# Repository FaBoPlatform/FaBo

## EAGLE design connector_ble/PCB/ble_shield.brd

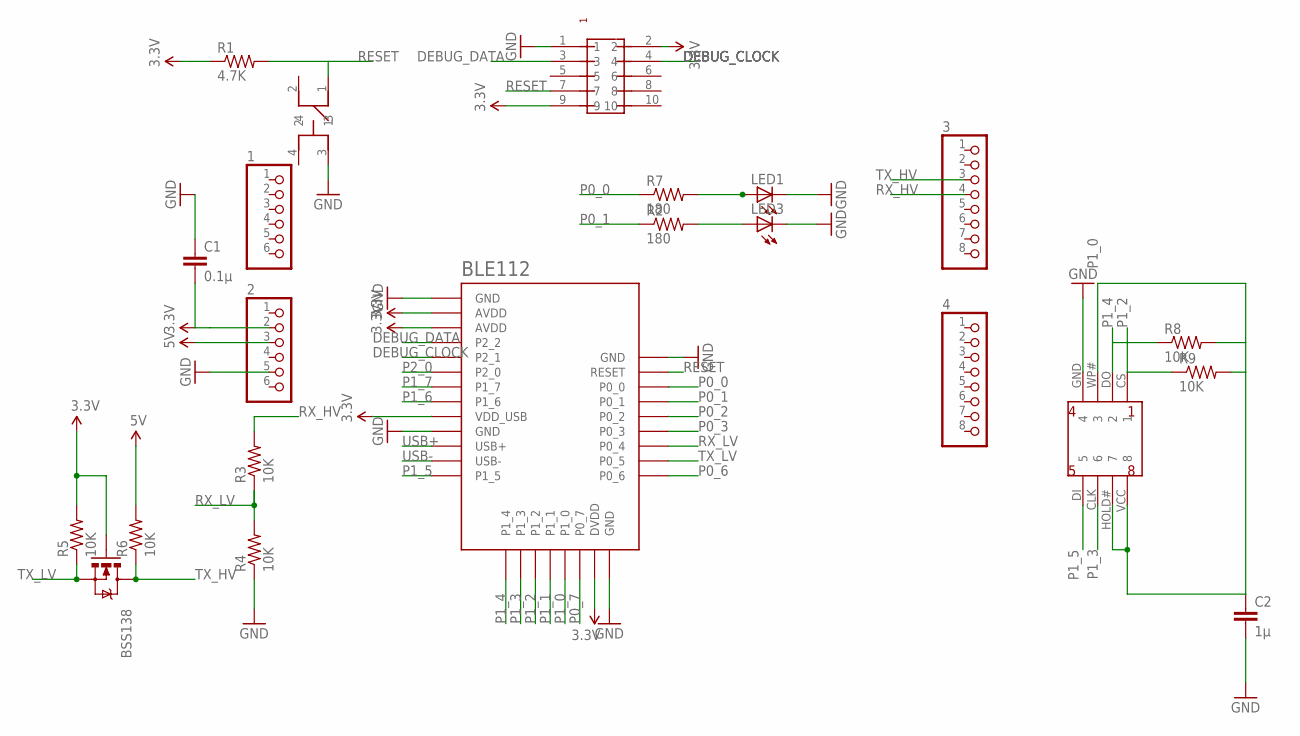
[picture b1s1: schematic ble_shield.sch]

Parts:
1, 2: PINHD-1X6CB; 1X06-CLEANBIG
3, 4: PINHD-1X8CLEANBIG; 1X08-CLEANBIG
BLE112: SF-BLUEGIGA_BLE112-A-VISUAL; SF-BLUEGIGA_BLE112-A
BSS138: MOSFET-NCHANNELSMD; SOT23-3
C1: 0.1μ; 0603-CAP
C2: 1μ; 0603-CAP
LED1, LED3: LED_ESML0603; LED_SML0603
R1: 4.7K; 0603-RES
R2, R7: 180; 0603-RES
R3, R4, R5, R6, R8, R9: 10K; 0603-RES
U$1: PIN-HEADER-SMT(1.27MM)2X5
U$4: SWITCH-LS6J2M-T; SWICTH-LS6J2M-T
U$7: FLASH-MEMORY-2M(WINBOND)

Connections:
3.3V: 2.2, BLE112.AVDD1 (AVDD), BLE112.AVDD2 (AVDD), BLE112.DVDD, BLE112.VDD_USB, BSS138.1 (G), C1.2, R1.1, R5.2, U$1.2, U$1.9
5V: 2.3, R6.2
DEBUG_CLOCK: BLE112.P2_1, U$1.4
DEBUG_DATA: BLE112.P2_2, U$1.3
GND: 2.5, BLE112.GND1 (GND), BLE112.GND2 (GND), BLE112.GND3 (GND), BLE112.GND4 (GND), C1.1, C2.2, LED1.C, LED3.C, R4.1, U$1.1, U$4.3, U$7.GND (4)
unnamed: LED1.A, R7.2
unnamed: LED3.A, R2.2
P0_0: BLE112.P0_0, R7.1
P0_1: BLE112.P0_1, R2.1
P0_2: BLE112.P0_2
P0_3: BLE112.P0_3
P0_6: BLE112.P0_6
P0_7: BLE112.P0_7
P1_0: BLE112.P1_0, C2.1, R8.2, R9.2, U$7.HOLD# (7), U$7.VCC (8), U$7.WP# (3)
P1_1: BLE112.P1_1
P1_2: BLE112.P1_2, R9.1, U$7.CS (1)
P1_3: BLE112.P1_3, U$7.CLK (6)
P1_4: BLE112.P1_4, R8.1, U$7.DO (2)
P1_5: BLE112.P1_5, U$7.DI (5)
P1_6: BLE112.P1_6
P1_7: BLE112.P1_7
P2_0: BLE112.P2_0
RESET: BLE112.RESET, R1.2, U$1.7, U$4.1
RX_HV: 3.4, R3.2
RX_LV: BLE112.P0_4, R3.1, R4.2
TX_HV: 3.3, BSS138.3 (D), R6.1
TX_LV: BLE112.P0_5, BSS138.2 (S), R5.1
USB+: BLE112.USB+
USB-: BLE112.USB-

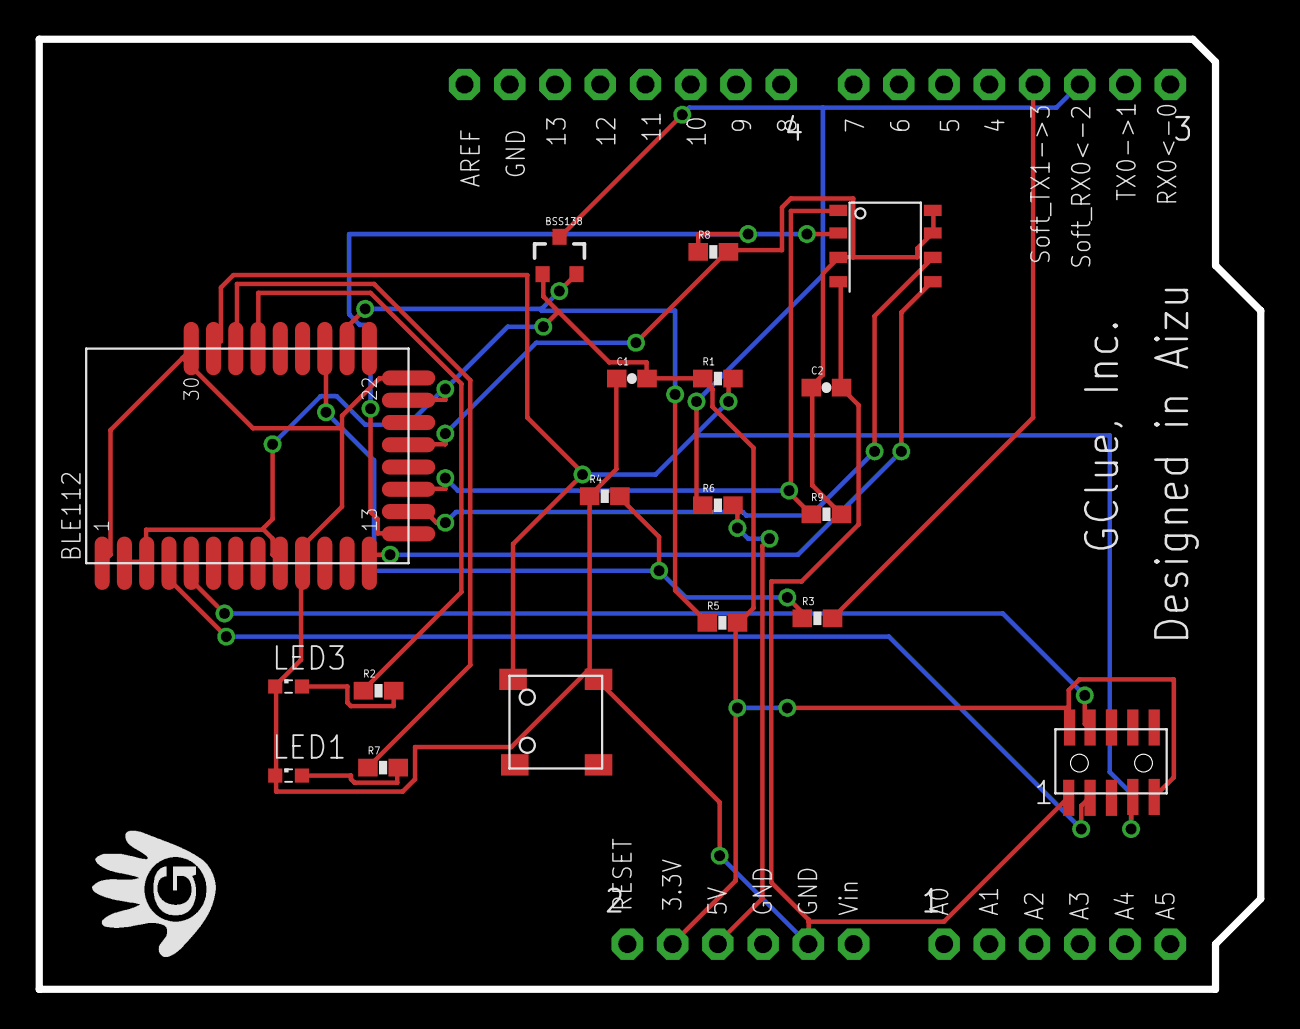
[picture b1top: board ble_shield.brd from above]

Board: 2 copper layers, 68.6 x 53.3 mm, 22 parts (0 on the bottom side), 19 nets.

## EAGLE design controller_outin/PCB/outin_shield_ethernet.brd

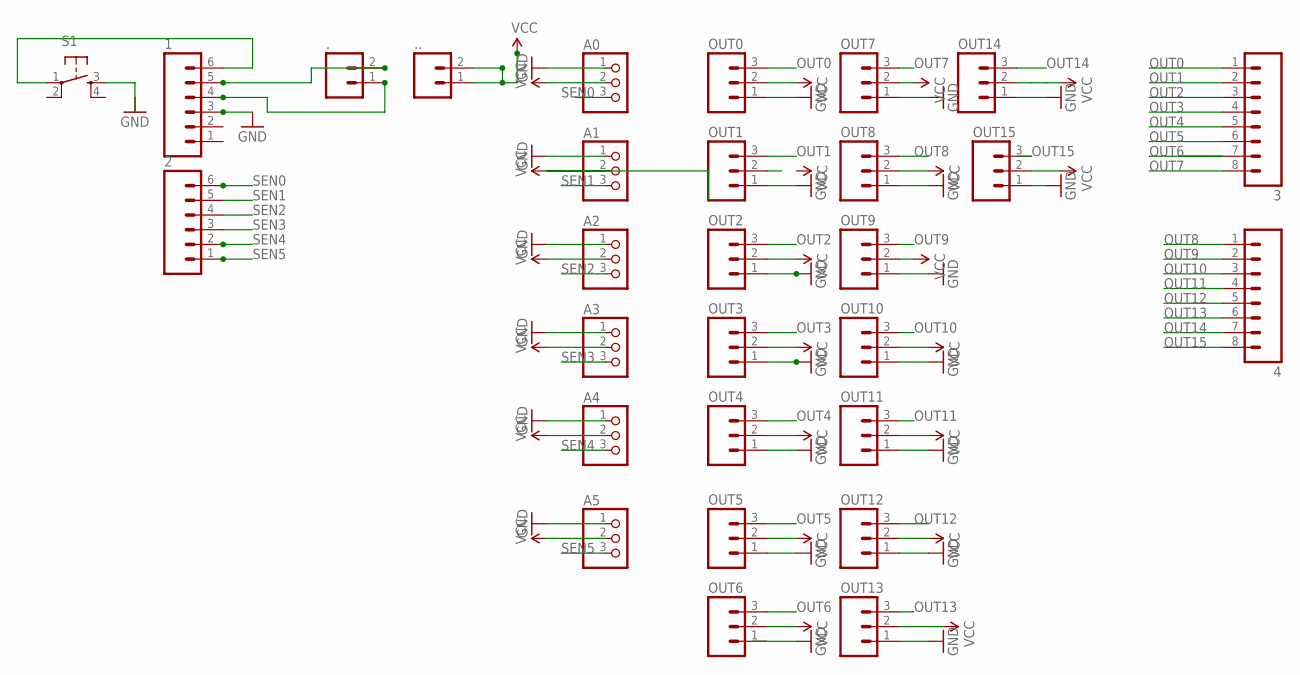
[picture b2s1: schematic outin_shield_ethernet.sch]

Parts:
1, 2: M06SIP; 1X06
3, 4: M081X08; 1X08
., ..: M02LOCK; 1X02_LOCK
A0, A1, A2, A3, A4, A5: PINHD-1X3; 1X03
OUT0, OUT1, OUT2, OUT3, OUT4, OUT5, OUT6, OUT7, OUT8, OUT9, OUT10, OUT11, OUT12, OUT13, OUT14, OUT15: M03PTH; 1X03
S1: TAC_SWITCHPTH; TACTILE-PTH

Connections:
GND: 1.3, A0.1, A1.1, A2.1, A3.1, A4.1, A5.1, OUT0.1, OUT1.1, OUT2.1, OUT3.1, OUT4.1, OUT5.1, OUT7.1, OUT8.1, OUT9.1, OUT10.1, OUT11.1, OUT12.1, OUT13.1, OUT14.1, OUT15.1
unnamed: 1.6, S1.1
unnamed: 1.4, ..1
unnamed: 1.5, ..2
OUT0: 3.1, OUT0.3
OUT1: 3.2, OUT1.3
OUT2: 3.3, OUT2.3
OUT3: 3.4, OUT3.3
OUT4: 3.5, OUT4.3
OUT5: 3.6, OUT5.3
OUT6: 3.7, OUT6.3
OUT7: 3.8, OUT7.3
OUT8: 4.1, OUT8.3
OUT9: 4.2, OUT9.3
OUT10: 4.3, OUT10.3
OUT11: 4.4, OUT11.3
OUT12: 4.5, OUT12.3
OUT13: 4.6, OUT13.3
OUT14: 4.7, OUT14.3
OUT15: 4.8, OUT15.3
SEN0: 2.6, A0.3
SEN1: 2.5, A1.3
SEN2: 2.4, A2.3
SEN3: 2.3, A3.3
SEN4: 2.2, A4.3
SEN5: 2.1, A5.3
VCC: ...1, ...2, A0.2, A1.2, A2.2, A3.2, A4.2, A5.2, OUT0.2, OUT2.2, OUT3.2, OUT4.2, OUT5.2, OUT6.2, OUT7.2, OUT8.2, OUT9.2, OUT10.2, OUT11.2, OUT12.2, OUT13.2, OUT14.2, OUT15.2

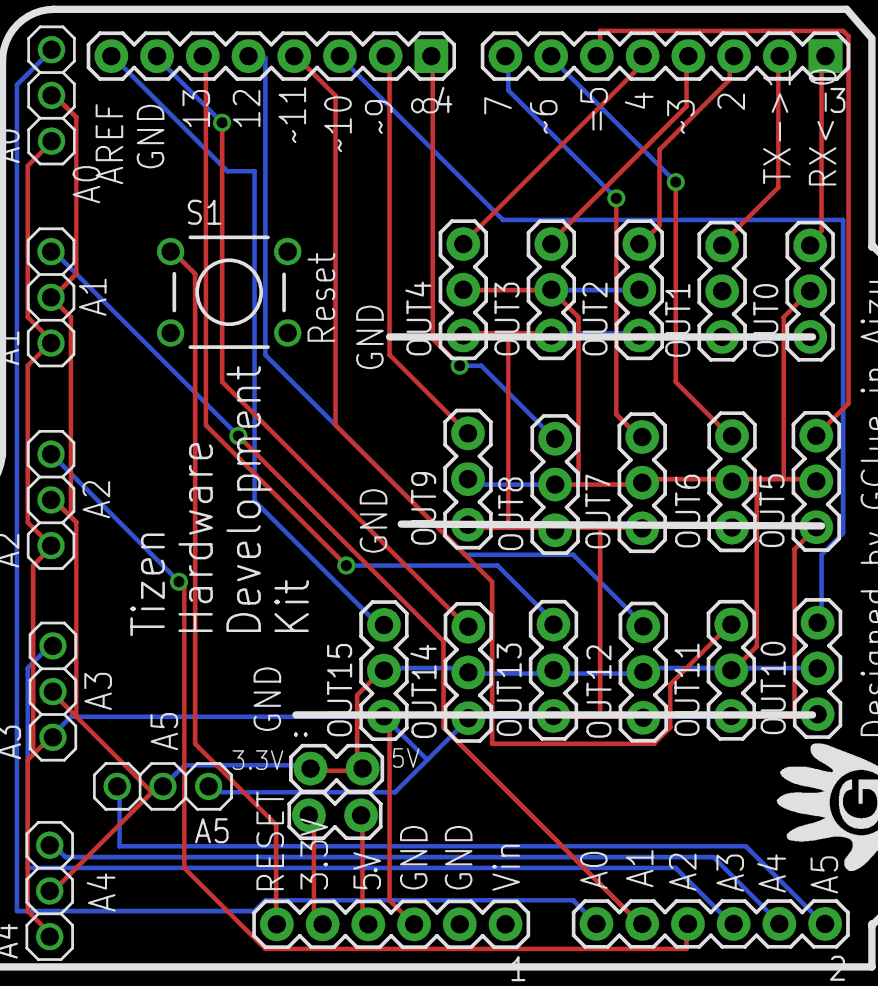
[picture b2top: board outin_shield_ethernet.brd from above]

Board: 2 copper layers, 29 parts (0 on the bottom side), 27 nets.

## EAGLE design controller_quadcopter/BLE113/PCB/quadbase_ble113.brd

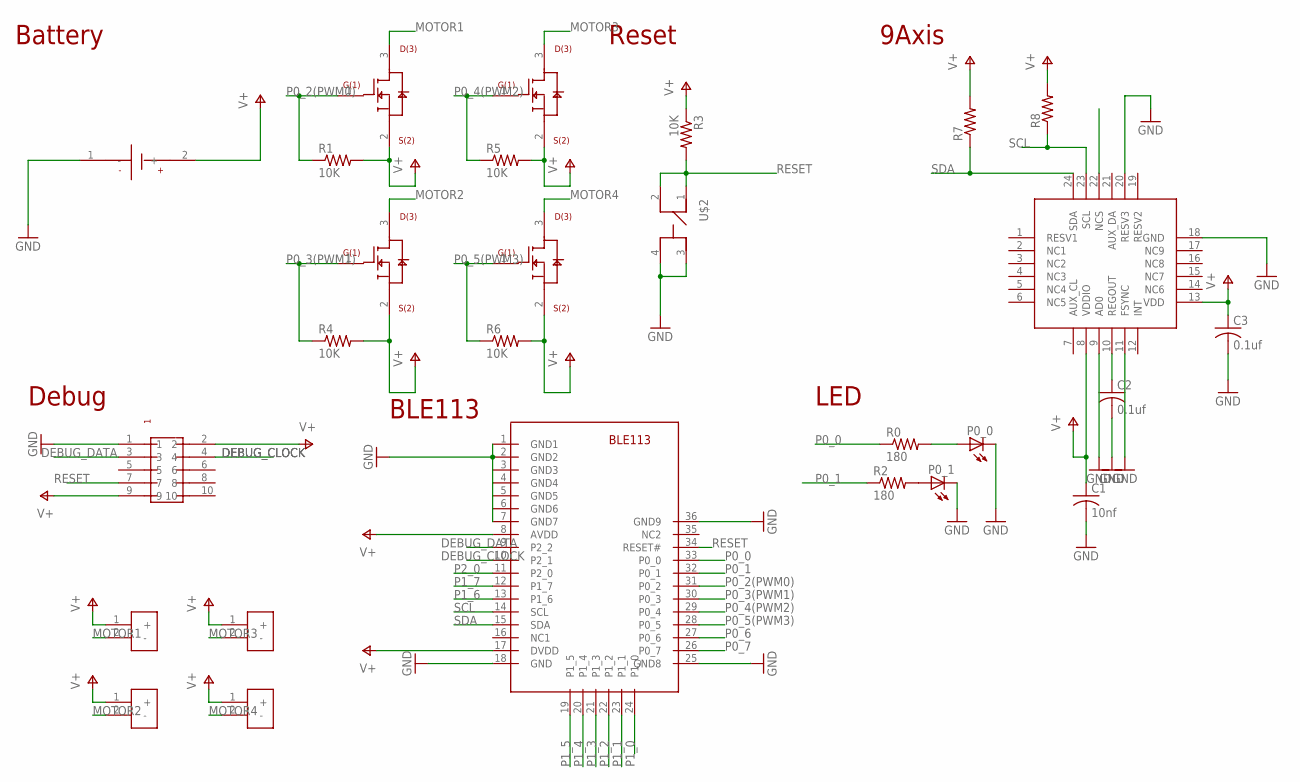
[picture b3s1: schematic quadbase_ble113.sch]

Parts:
C1: 10nf; C0603
C2, C3: 0.1uf; C0603
MOTOR1, MOTOR2, MOTOR3, MOTOR4: SMD-MOTOR
P0_0, P0_1: LEDCHIP-LED0603; CHIP-LED0603
R0, R2: 180; 0603-RES
R1, R4, R5, R6: 10K; R0603
R3: 10K; 0603-RES
R7, R8: R-US_R0603; R0603
U$1: SMD-SUPPLY; SMD_SUPPLY
U$2: SWITCH-LS6J2M-T
U$3: PIN-HEADER-SMT(1.27MM)2X5
U$4: BLE113
U$5, U$7, U$8, U$9: VISHAY-SI2318CDS
U$10: INVENSENSE-MPU9250

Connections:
DEBUG_CLOCK: U$3.4, U$4.10 (P2_1)
DEBUG_DATA: U$3.3, U$4.9 (P2_2)
GND: C1.2, C2.2, C3.2, P0_0.C, P0_1.C, U$1.1 (-), U$2.3, U$2.4, U$3.1, U$4.1 (GND1), U$4.2 (GND2), U$4.3 (GND3), U$4.4 (GND4), U$4.5 (GND5), U$4.6 (GND6), U$4.7 (GND7), U$4.18 (GND), U$4.25 (GND8), U$4.36 (GND9), U$10.9 (AD0), U$10.11 (FSYNC), U$10.18 (GND), U$10.20 (RESV3)
MOTOR1: MOTOR1.2 (-), U$5.3
MOTOR2: MOTOR2.2 (-), U$7.3
MOTOR3: MOTOR3.2 (-), U$8.3
MOTOR4: MOTOR4.2 (-), U$9.3
unnamed: C2.1, U$10.10 (REGOUT)
unnamed: P0_0.A, R0.2
unnamed: P0_1.A, R2.2
P0_0: R0.1, U$4.33 (P0_0)
P0_1: R2.1, U$4.32 (P0_1)
P0_2(PWM0): R1.1, U$4.31 (P0_2), U$5.1
P0_3(PWM1): R4.1, U$4.30 (P0_3), U$7.1
P0_4(PWM2): R5.1, U$4.29 (P0_4), U$8.1
P0_5(PWM3): R6.1, U$4.28 (P0_5), U$9.1
P0_6: U$4.27 (P0_6)
P0_7: U$4.26 (P0_7)
P1_0: U$4.24 (P1_0)
P1_1: U$4.23 (P1_1)
P1_2: U$4.22 (P1_2)
P1_3: U$4.21 (P1_3)
P1_4: U$4.20 (P1_4)
P1_5: U$4.19 (P1_5)
P1_6: U$4.13 (P1_6)
P1_7: U$4.12 (P1_7)
P2_0: U$4.11 (P2_0)
RESET: R3.2, U$2.1, U$2.2, U$3.7, U$4.34 (RESET#)
SCL: R8.1, U$4.14 (SCL), U$10.23 (SCL)
SDA: R7.1, U$4.15 (SDA), U$10.24 (SDA)
V+: C1.1, C3.1, MOTOR1.1 (+), MOTOR2.1 (+), MOTOR3.1 (+), MOTOR4.1 (+), R1.2, R3.1, R4.2, R5.2, R6.2, R7.2, R8.2, U$1.2 (+), U$3.2, U$3.9, U$4.8 (AVDD), U$4.17 (DVDD), U$5.2, U$7.2, U$8.2, U$9.2, U$10.8 (VDDIO), U$10.13 (VDD)

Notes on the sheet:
Reset
Battery
Debug
BLE113
LED
9Axis

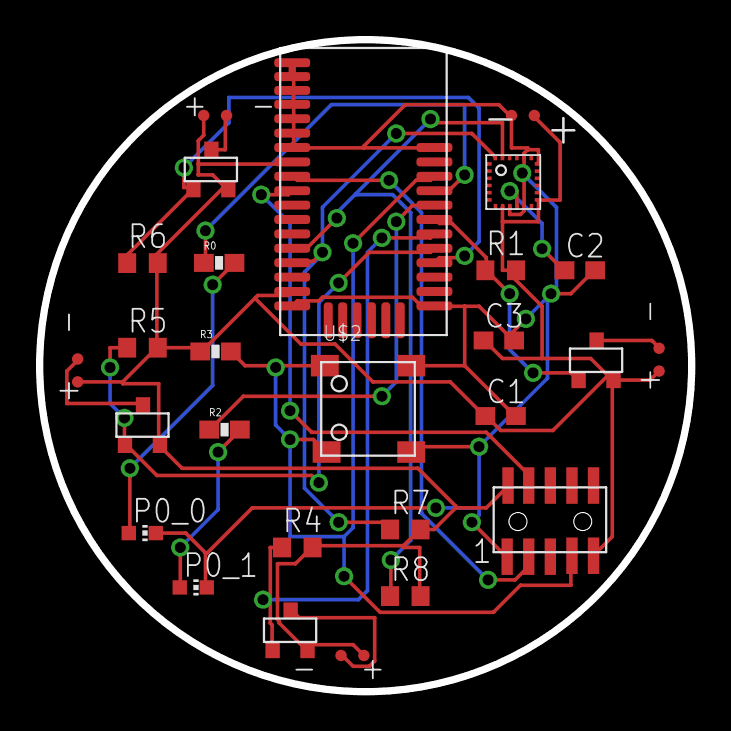
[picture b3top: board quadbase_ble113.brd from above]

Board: 2 copper layers, 36.2 x 36.2 mm, 27 parts (0 on the bottom side), 20 nets.

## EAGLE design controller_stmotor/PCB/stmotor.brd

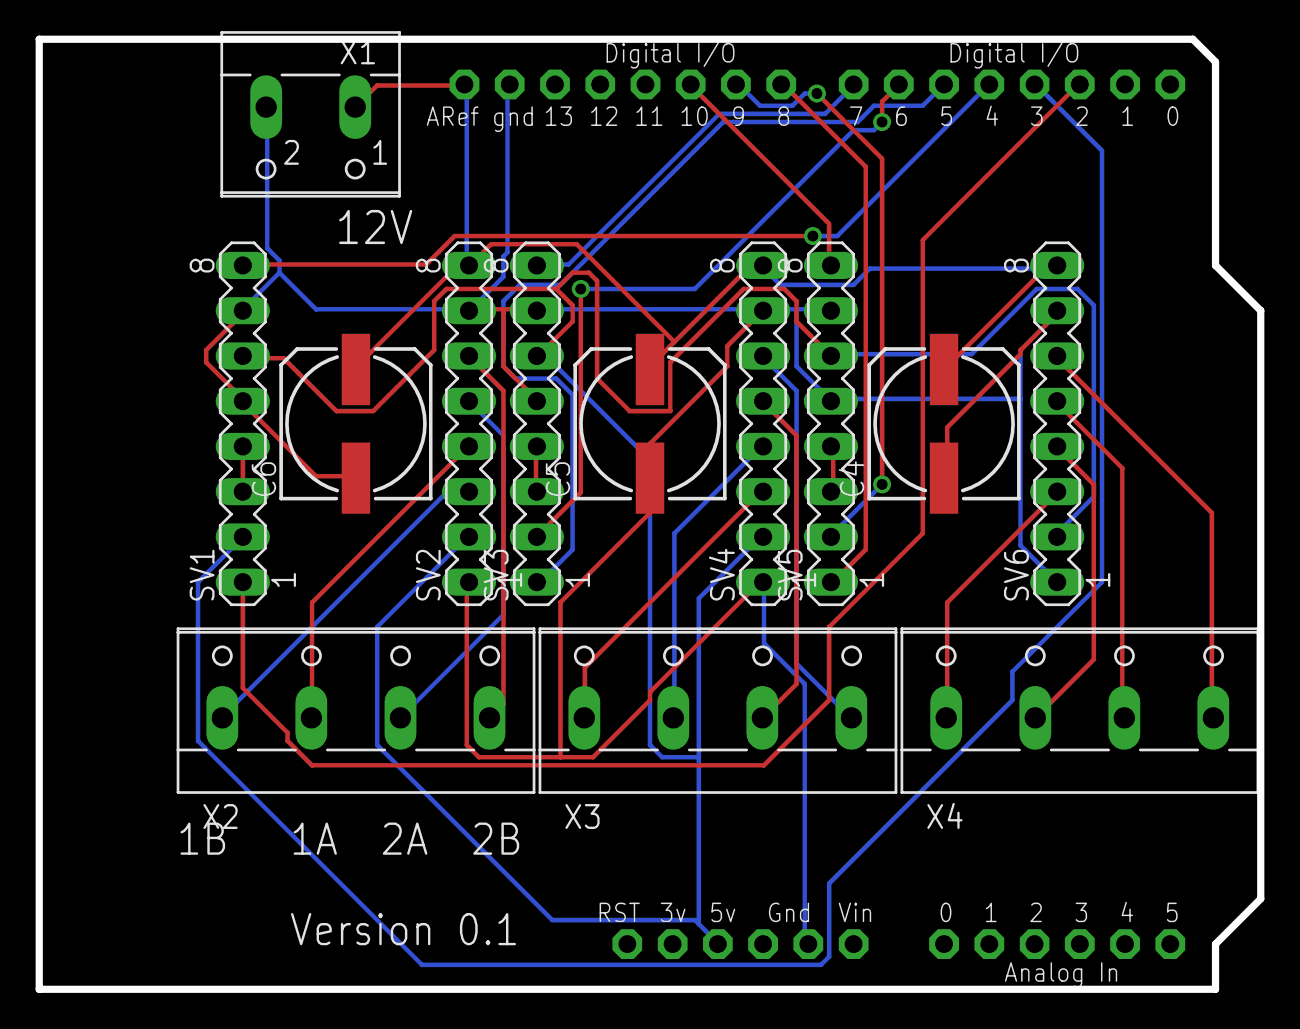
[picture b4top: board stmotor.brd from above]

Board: 2 copper layers, 68.6 x 53.3 mm, 14 parts (0 on the bottom side), 27 nets.

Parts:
C4, C5, C6: 153CLV-0807
SV1, SV2, SV3, SV4, SV5, SV6: MA08-1
U$1: ARDUINO-NOHOLE
X1: W237-102
X2, X3, X4: W237-4

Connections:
+5V: SV1.6, SV2.2, SV3.6, SV4.2, SV5.6, SV6.2, U$1.5V
+12V: C4.+, C5.+, C6.+, SV2.8, SV4.8, SV6.8, U$1.AREF, X1.1
GND: C4.-, C5.-, C6.-, SV1.5, SV1.7, SV2.1, SV2.7, SV3.5, SV3.7, SV4.1, SV4.7, SV5.5, SV5.7, SV6.1, SV6.7, U$1.GND, U$1.GND1, X1.2
unnamed: SV3.3, SV3.4
unnamed: SV5.3, SV5.4
S1_1A: SV2.4, X2.2
S1_1B: SV2.3, X2.1
S1_2A: SV2.5, X2.3
S1_2B: SV2.6, X2.4
S1_DIR: SV1.1, U$1.D2
S1_EN: SV1.8, U$1.D4
S1_RST: SV1.3, SV1.4
S1_STEP: SV1.2, U$1.D3
S2_1A: SV4.4, X3.2
S2_1B: SV4.3, X3.1
S2_2A: SV4.5, X3.3
S2_2B: SV4.6, X3.4
S2_DIR: SV3.1, U$1.D5
S2_EN: SV3.8, U$1.D7
S2_STEP: SV3.2, U$1.D6
S3_1A: SV6.4, X4.2
S3_1B: SV6.3, X4.1
S3_2A: SV6.5, X4.3
S3_2B: SV6.6, X4.4
S3_DIR: SV5.1, U$1.D8
S3_EN: SV5.8, U$1.D10
S3_STEP: SV5.2, U$1.D9

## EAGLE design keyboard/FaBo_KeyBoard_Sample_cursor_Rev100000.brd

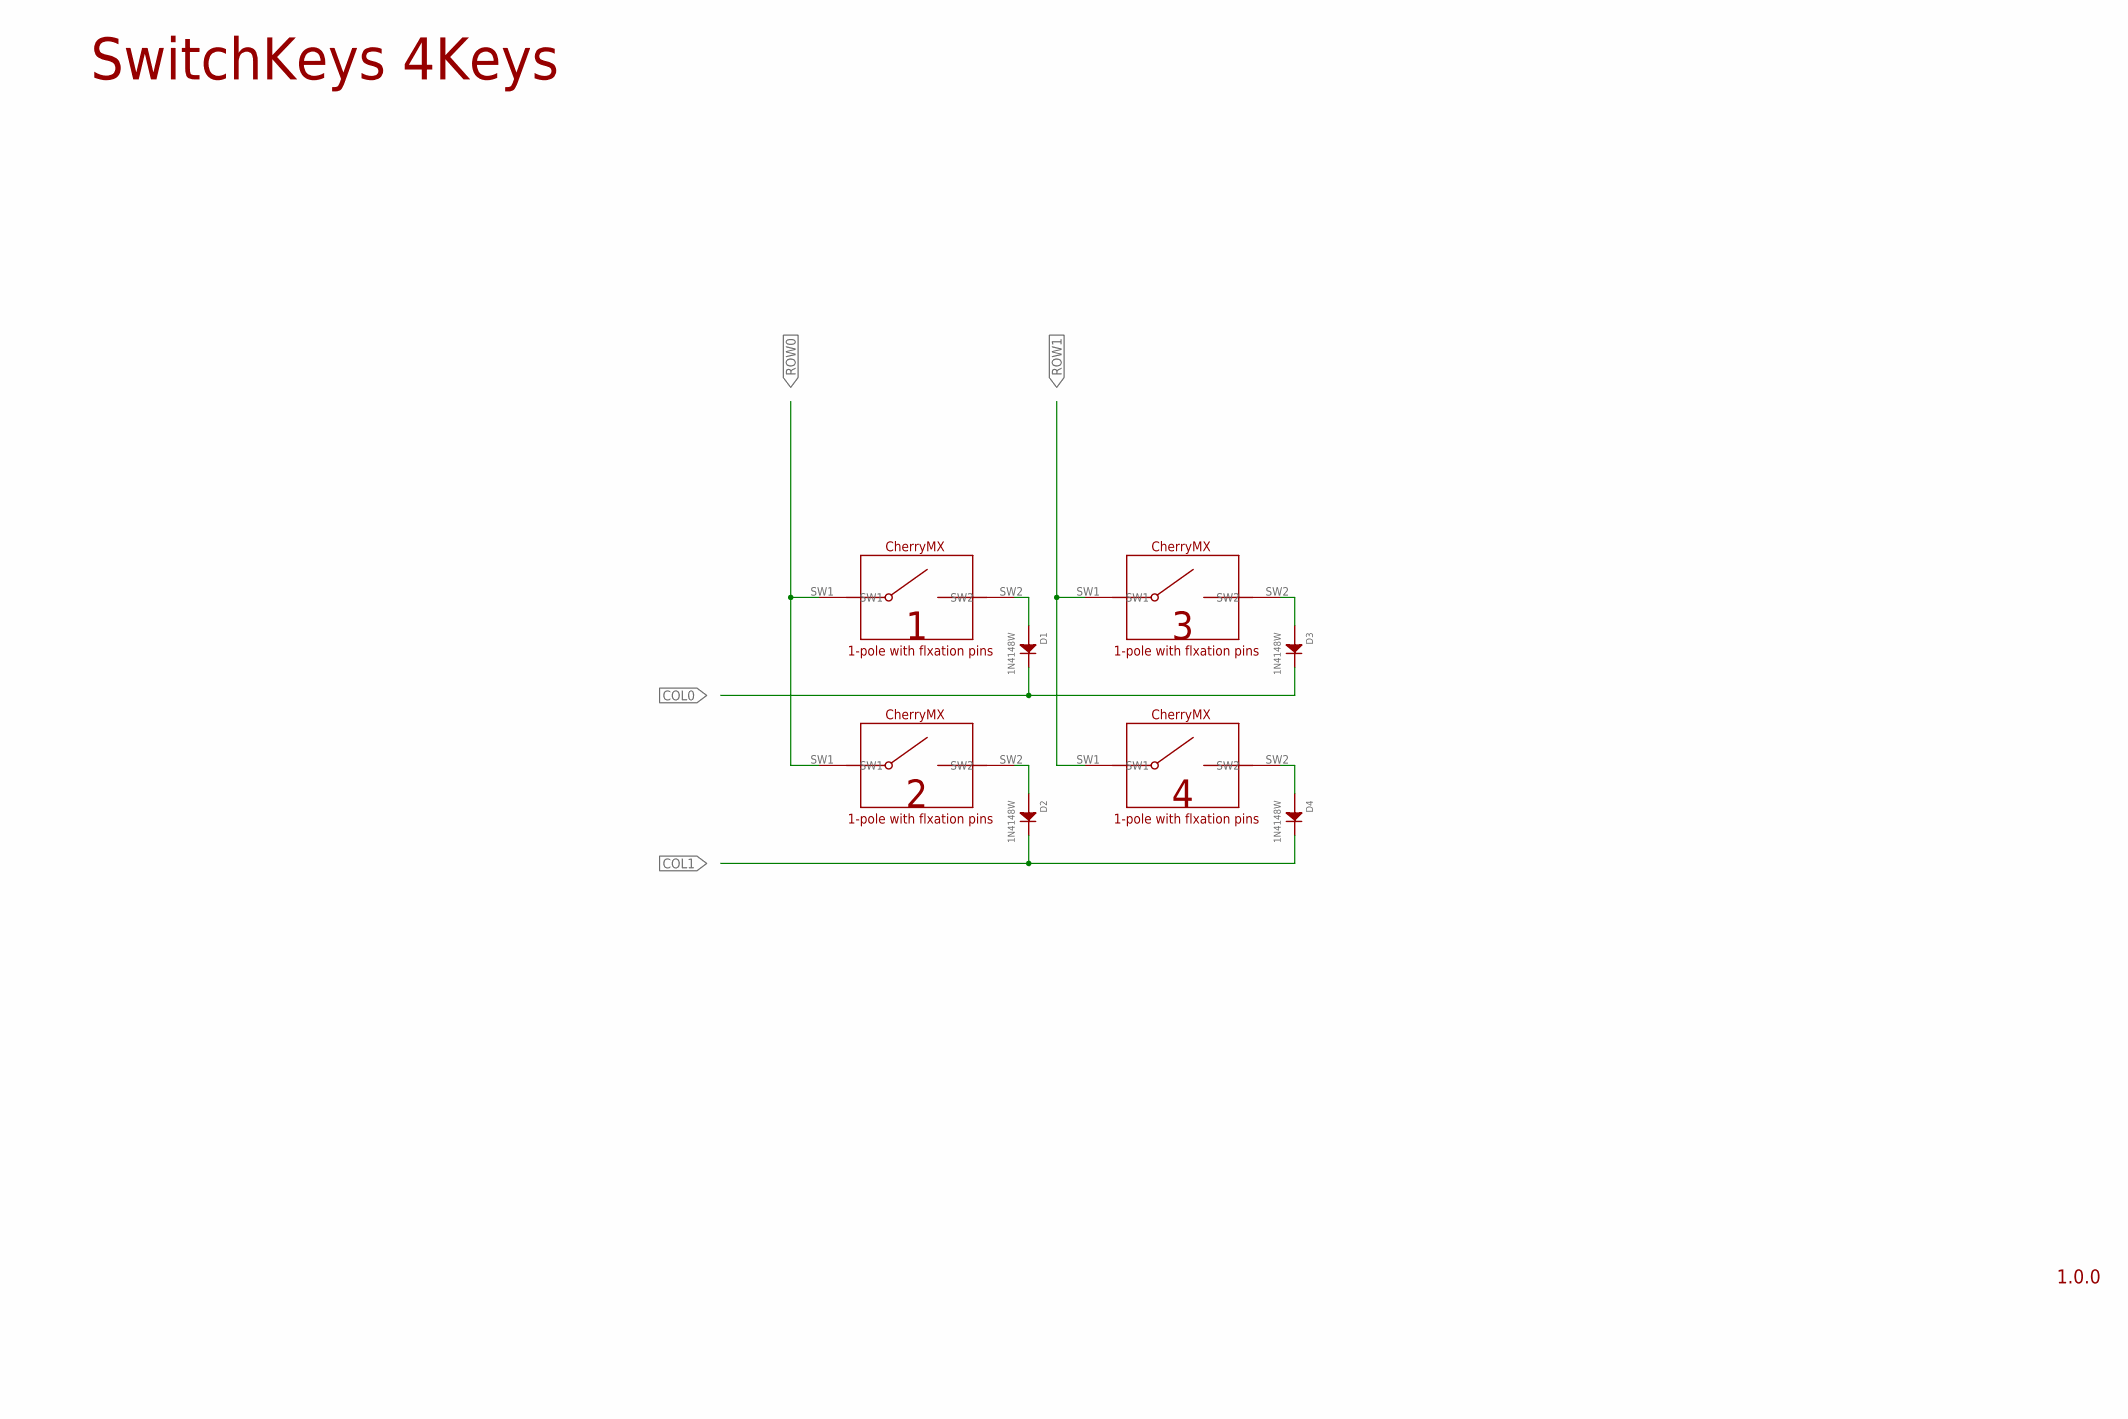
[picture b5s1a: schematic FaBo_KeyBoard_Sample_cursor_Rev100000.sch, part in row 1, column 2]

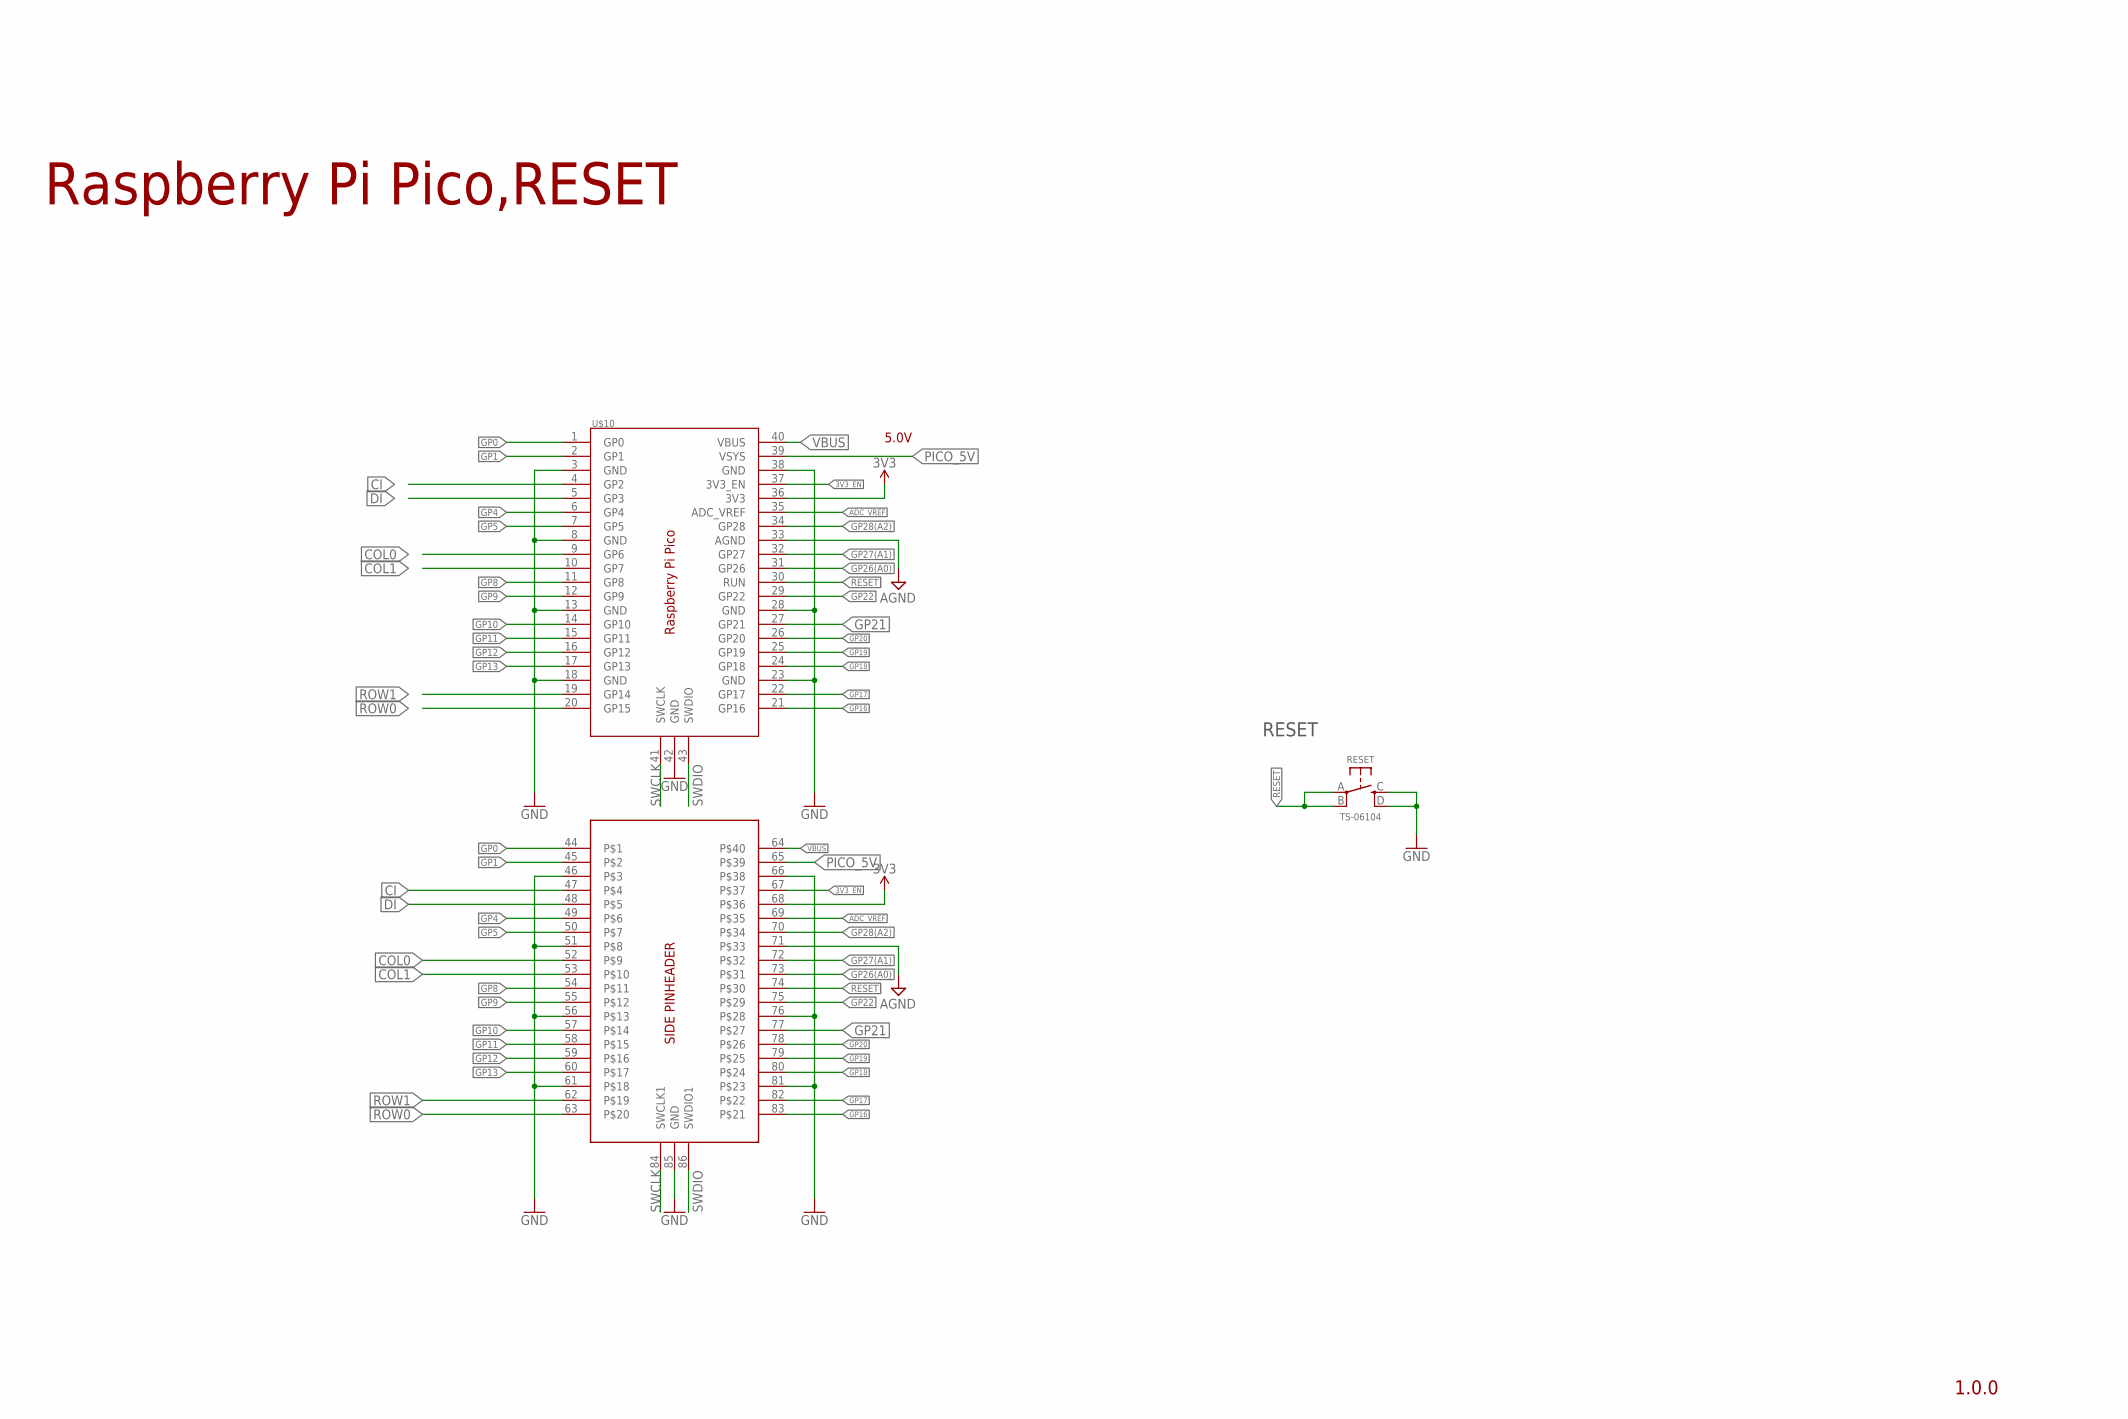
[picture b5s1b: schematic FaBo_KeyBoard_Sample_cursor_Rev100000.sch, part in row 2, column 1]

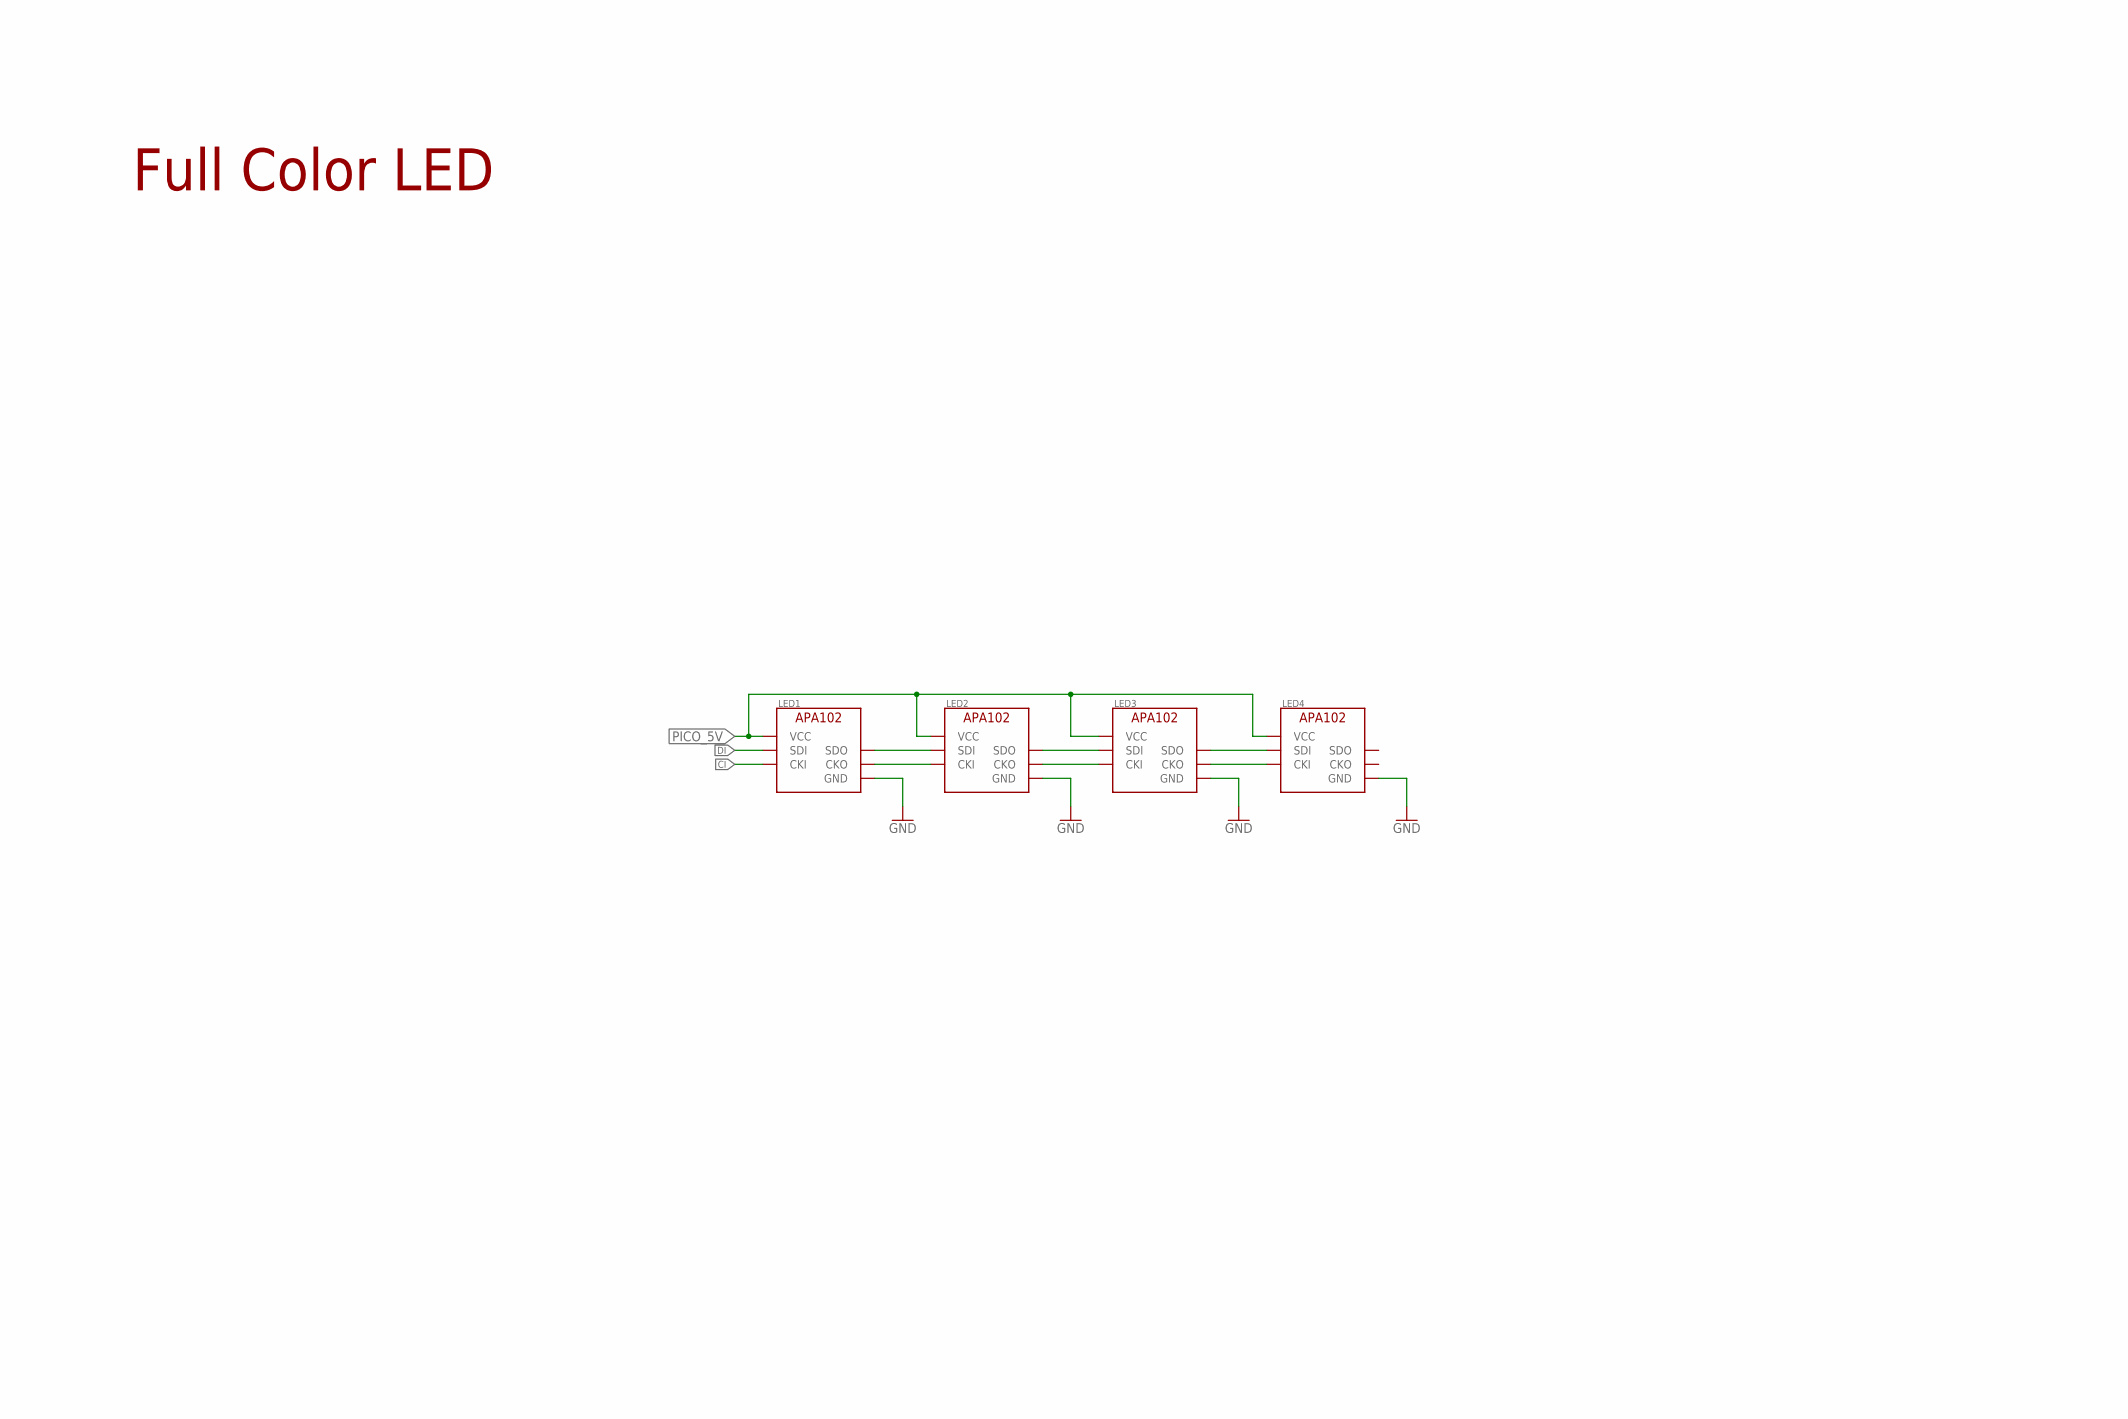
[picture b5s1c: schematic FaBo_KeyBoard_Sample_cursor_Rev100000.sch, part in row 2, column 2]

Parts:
D1, D2, D3, D4: 1N4148W; SOD-123
LED1, LED2, LED3, LED4: APA102_IPIXEL; APA102_2020
RESET: TS-06104
SW1, SW2, SW3, SW4: CHERRYMX_1-POLE_FLXATION_PINS
U$10: RASPBERRY_PI_PICO_BOTH_TH_PINHEADER; RASPBERRY_PI_PICO_HEADER_BOTH

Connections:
3V3: U$10.36 (3V3), U$10.68
3V3_EN: U$10.37 (3V3_EN), U$10.67
ADC_VREF: U$10.35 (ADC_VREF), U$10.69
AGND: U$10.33 (AGND), U$10.71
CI: LED1.CKI, U$10.4 (GP2), U$10.47
CI1: LED1.CKO, LED2.CKI
CI2: LED2.CKO, LED3.CKI
CI3: LED3.CKO, LED4.CKI
COL0: D1.1 (CATHODE), D3.1 (CATHODE), U$10.9 (GP6), U$10.52
COL1: D2.1 (CATHODE), D4.1 (CATHODE), U$10.10 (GP7), U$10.53
DI: LED1.SDI, U$10.5 (GP3), U$10.48
DI1: LED1.SDO, LED2.SDI
DI2: LED2.SDO, LED3.SDI
DI3: LED3.SDO, LED4.SDI
GND: LED1.GND, LED2.GND, LED3.GND, LED4.GND, RESET.C, RESET.D, U$10.3 (GND), U$10.8 (GND), U$10.13 (GND), U$10.18 (GND), U$10.23 (GND), U$10.28 (GND), U$10.38 (GND), U$10.42 (GND), U$10.46, U$10.51, U$10.56, U$10.61, U$10.66, U$10.76, U$10.81, U$10.85 (GND)
GP0: U$10.1 (GP0), U$10.44
GP1: U$10.2 (GP1), U$10.45
GP4: U$10.6 (GP4), U$10.49
GP5: U$10.7 (GP5), U$10.50
GP8: U$10.11 (GP8), U$10.54
GP9: U$10.12 (GP9), U$10.55
GP10: U$10.14 (GP10), U$10.57
GP11: U$10.15 (GP11), U$10.58
GP12: U$10.16 (GP12), U$10.59
GP13: U$10.17 (GP13), U$10.60
GP16: U$10.21 (GP16), U$10.83
GP17: U$10.22 (GP17), U$10.82
GP18: U$10.24 (GP18), U$10.80
GP19: U$10.25 (GP19), U$10.79
GP20: U$10.26 (GP20), U$10.78
GP21: U$10.27 (GP21), U$10.77
GP22: U$10.29 (GP22), U$10.75
GP26(A0): U$10.31 (GP26), U$10.73
GP27(A1): U$10.32 (GP27), U$10.72
GP28(A2): U$10.34 (GP28), U$10.70
unnamed: D1.2 (ANODE), SW1.SW2
unnamed: D2.2 (ANODE), SW2.SW2
unnamed: D3.2 (ANODE), SW3.SW2
unnamed: D4.2 (ANODE), SW4.SW2
PICO_5V: LED1.VCC, LED2.VCC, LED3.VCC, LED4.VCC, U$10.39 (VSYS), U$10.65
RESET: RESET.A, RESET.B, U$10.30 (RUN), U$10.74
ROW0: SW1.SW1, SW2.SW1, U$10.20 (GP15), U$10.63
ROW1: SW3.SW1, SW4.SW1, U$10.19 (GP14), U$10.62
SWCLK: U$10.41 (SWCLK), U$10.84 (SWCLK1)
SWDIO: U$10.43 (SWDIO), U$10.86 (SWDIO1)
VBUS: U$10.40 (VBUS), U$10.64

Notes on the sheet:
1.0.0
Revision
Raspberry Pi Pico,RESET
SwitchKeys 4Keys
1.0.0
FaBo KeyBoard Sample
RESET
5.0V
Full Color LED

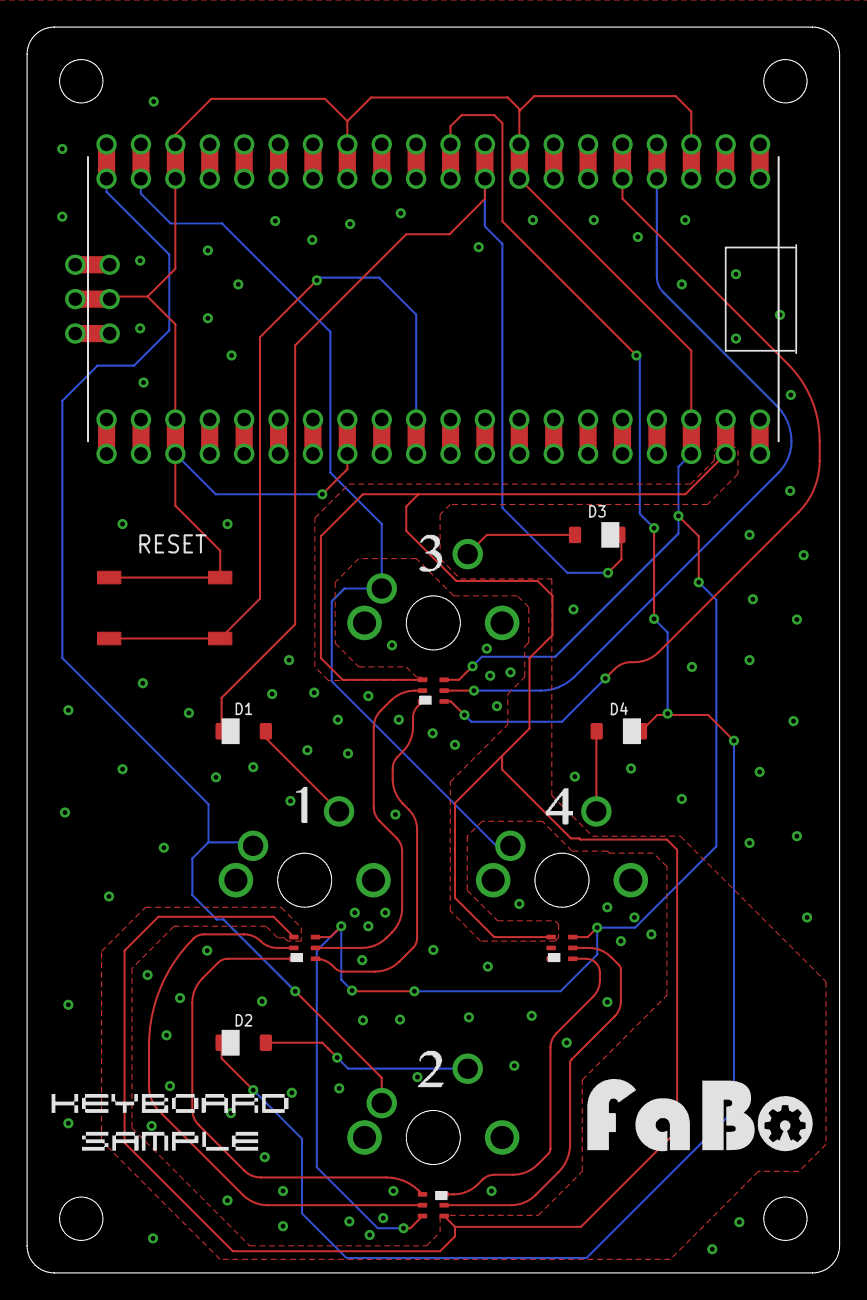
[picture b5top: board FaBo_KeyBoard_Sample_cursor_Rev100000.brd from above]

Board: 2 copper layers, 60.0 x 92.0 mm, 15 parts (0 on the bottom side), 46 nets.

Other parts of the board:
U$1: LOGO_FABO_L

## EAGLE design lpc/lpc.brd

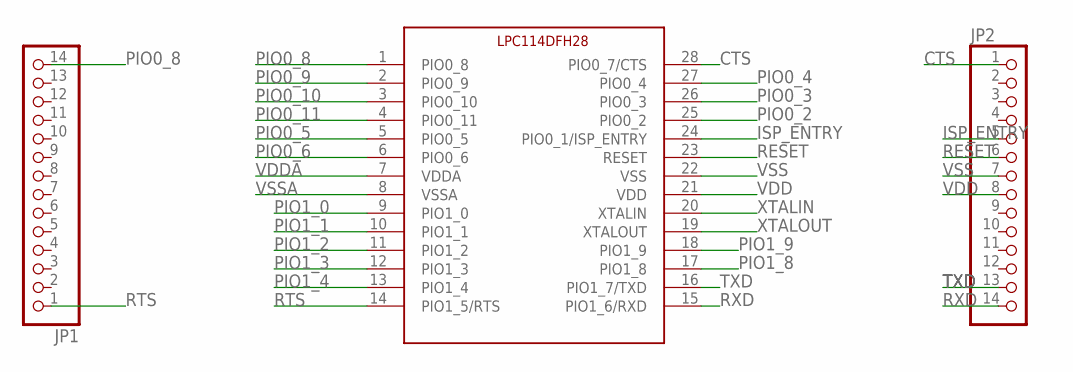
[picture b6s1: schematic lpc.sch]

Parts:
JP1, JP2: PINHD-1X14-CB; 1X14-CB
U$1: MUC-LPC1114

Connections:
CTS: JP2.1, U$1.28 (PIO0_7/CTS)
ISP_ENTRY: JP2.5, U$1.24 (PIO0_1/ISP_ENTRY)
PIO0_2: U$1.25 (PIO0_2)
PIO0_3: U$1.26 (PIO0_3)
PIO0_4: U$1.27 (PIO0_4)
PIO0_5: U$1.5 (PIO0_5)
PIO0_6: U$1.6 (PIO0_6)
PIO0_8: JP1.14, U$1.1 (PIO0_8)
PIO0_9: U$1.2 (PIO0_9)
PIO0_10: U$1.3 (PIO0_10)
PIO0_11: U$1.4 (PIO0_11)
PIO1_0: U$1.9 (PIO1_0)
PIO1_1: U$1.10 (PIO1_1)
PIO1_2: U$1.11 (PIO1_2)
PIO1_3: U$1.12 (PIO1_3)
PIO1_4: U$1.13 (PIO1_4)
PIO1_8: U$1.17 (PIO1_8)
PIO1_9: U$1.18 (PIO1_9)
RESET: JP2.6, U$1.23 (RESET)
RTS: JP1.1, U$1.14 (PIO1_5/RTS)
RXD: JP2.14, U$1.15 (PIO1_6/RXD)
TXD: JP2.13, U$1.16 (PIO1_7/TXD)
VDD: JP2.8, U$1.21 (VDD)
VDDA: U$1.7 (VDDA)
VSS: JP2.7, U$1.22 (VSS)
VSSA: U$1.8 (VSSA)
XTALIN: U$1.20 (XTALIN)
XTALOUT: U$1.19 (XTALOUT)

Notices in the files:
parts and their libraries:
SparkFun: Licensing: CC v3.0 Share-Alike You are welcome to use this library for commercial purposes.
FaBo-Keyboard: Released under the Creative Commons Attribution-ShareAlike 4.0 License
https://creativecommons.org/licenses/by-sa/4.0
